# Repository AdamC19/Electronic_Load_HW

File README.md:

# Electronic_Load_HW
Hardware source files for my multi-channel electronic load. Read more about this device [here](http://www.acordingley.us/electronic-load/).
## Electronic_Load_Controller/
Files for the controller, of which there should be 1 per electronic load.
## Electronic_Load_Module/
Files for the modules/channels. I designed it to have 8 of these per electronic load.

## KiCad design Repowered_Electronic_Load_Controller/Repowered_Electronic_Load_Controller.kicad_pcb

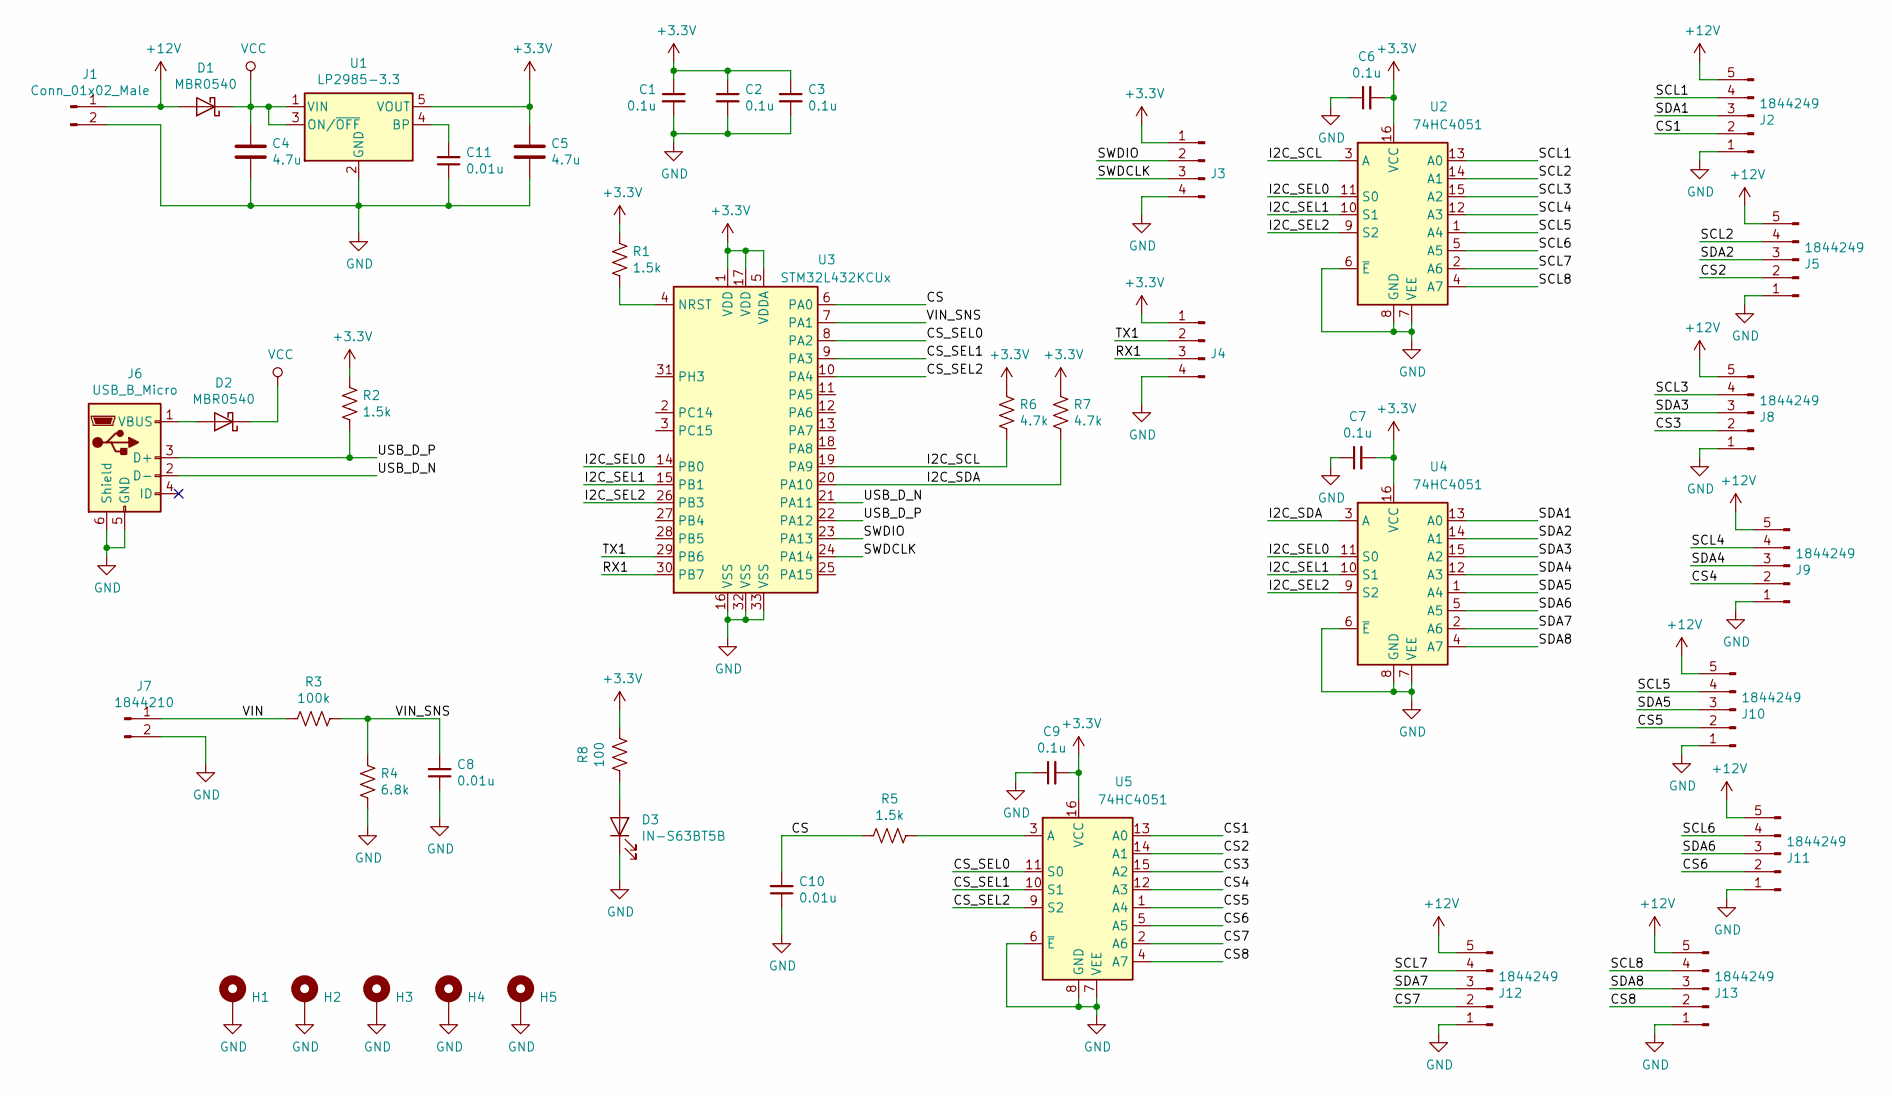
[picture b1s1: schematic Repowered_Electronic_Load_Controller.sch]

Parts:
C1, C2, C3, C6, C7, C9: 0.1u; C_0603_1608Metric
C4, C5: 4.7u; C_0805_2012Metric
C8, C10, C11: 0.01u; C_0603_1608Metric
D1, D2: MBR0540; D_SOD-123
D3: IN-S63BT5B; LED_0603_1608Metric
H1, H2, H3, H4, H5: MountingHole_Pad; MountingHole_2.5mm_Pad
J1: Conn_01x02_Male; PhoenixContact_MC_1,5_2-G-3.5_1x02_P3.50mm_Horizontal
J2, J5, J8, J9, J10, J11, J12, J13: 1844249; PhoenixContact_MC_1,5_5-G-3.5_1x05_P3.50mm_Horizontal
J3, J4: Conn_01x04_Male; PinHeader_1x04_P2.54mm_Vertical
J6: USB_B_Micro; USB_Micro-B_Molex-105017-0001
J7: 1844210; PhoenixContact_MC_1,5_2-G-3.5_1x02_P3.50mm_Horizontal
R1, R2, R5: 1.5k; R_0805_2012Metric
R3: 100k; R_0805_2012Metric
R4: 6.8k; R_0805_2012Metric
R6, R7: 4.7k; R_0805_2012Metric
R8: 100; R_0805_2012Metric
U1: LP2985-3.3; SOT-23-5
U2, U4, U5: 74HC4051; SOIC-16_3.9x9.9mm_P1.27mm
U3: STM32L432KCUx; QFN-32-1EP_5x5mm_P0.5mm_EP3.45x3.45mm

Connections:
+3V3: C1.1, C2.1, C3.1, C5.1, C6.2, C7.2, C9.2, J3.1, J4.1, R1.1, R2.1, R6.1, R7.1, R8.2, U1.5 (VOUT), U2.16 (VCC), U3.1 (VDD), U3.5 (VDDA), U3.17 (VDD), U4.16 (VCC), U5.16 (VCC)
+12V: D1.2 (A), J1.1, J2.5, J5.5, J8.5, J9.5, J10.5, J11.5, J12.5, J13.5
/CS: C10.2, R5.1, U3.6 (PA0)
/CS1: J2.2, U5.13 (A0)
/CS2: J5.2, U5.14 (A1)
/CS3: J8.2, U5.15 (A2)
/CS4: J9.2, U5.12 (A3)
/CS5: J10.2, U5.1 (A4)
/CS6: J11.2, U5.5 (A5)
/CS7: J12.2, U5.2 (A6)
/CS8: J13.2, U5.4 (A7)
/CS_SEL0: U3.8 (PA2), U5.11 (S0)
/CS_SEL1: U3.9 (PA3), U5.10 (S1)
/CS_SEL2: U3.10 (PA4), U5.9 (S2)
/I2C_SCL: R6.2, U2.3 (A), U3.19 (PA9)
/I2C_SDA: R7.2, U3.20 (PA10), U4.3 (A)
/I2C_SEL0: U2.11 (S0), U3.14 (PB0), U4.11 (S0)
/I2C_SEL1: U2.10 (S1), U3.15 (PB1), U4.10 (S1)
/I2C_SEL2: U2.9 (S2), U3.26 (PB3), U4.9 (S2)
/RX1: J4.3, U3.30 (PB7)
/SCL1: J2.4, U2.13 (A0)
/SCL2: J5.4, U2.14 (A1)
/SCL3: J8.4, U2.15 (A2)
/SCL4: J9.4, U2.12 (A3)
/SCL5: J10.4, U2.1 (A4)
/SCL6: J11.4, U2.5 (A5)
/SCL7: J12.4, U2.2 (A6)
/SCL8: J13.4, U2.4 (A7)
/SDA1: J2.3, U4.13 (A0)
/SDA2: J5.3, U4.14 (A1)
/SDA3: J8.3, U4.15 (A2)
/SDA4: J9.3, U4.12 (A3)
/SDA5: J10.3, U4.1 (A4)
/SDA6: J11.3, U4.5 (A5)
/SDA7: J12.3, U4.2 (A6)
/SDA8: J13.3, U4.4 (A7)
/SWDCLK: J3.3, U3.24 (PA14)
/SWDIO: J3.2, U3.23 (PA13)
/TX1: J4.2, U3.29 (PB6)
/USB_D_N: J6.2 (D-), U3.21 (PA11)
/USB_D_P: J6.3 (D+), R2.2, U3.22 (PA12)
/VIN: J7.1, R3.1
/VIN_SNS: C8.2, R3.2, R4.2, U3.7 (PA1)
GND: C1.2, C2.2, C3.2, C4.2, C5.2, C6.1, C7.1, C8.1, C9.1, C10.1, C11.1, D3.1 (K), H1.1, H2.1, H3.1, H4.1, H5.1, J1.2, J2.1, J3.4, J4.4, J5.1, J6.5 (GND), J6.6 (Shield), J7.2, J8.1, J9.1, J10.1, J11.1, J12.1, J13.1, R4.1, U1.2 (GND), U2.6 (~E), U2.7 (VEE), U2.8 (GND), U3.16 (VSS), U3.32 (VSS), U3.33 (VSS), U4.6 (~E), U4.7 (VEE), U4.8 (GND), U5.6 (~E), U5.7 (VEE), U5.8 (GND)
unnamed: C11.2, U1.4 (BP)
unnamed: D2.2 (A), J6.1 (VBUS)
unnamed: D3.2 (A), R8.1
unnamed: R1.2, U3.4 (NRST)
unnamed: R5.2, U5.3 (A)
VCC: C4.1, D1.1 (K), D2.1 (K), U1.1 (VIN), U1.3 (ON/~OFF~)

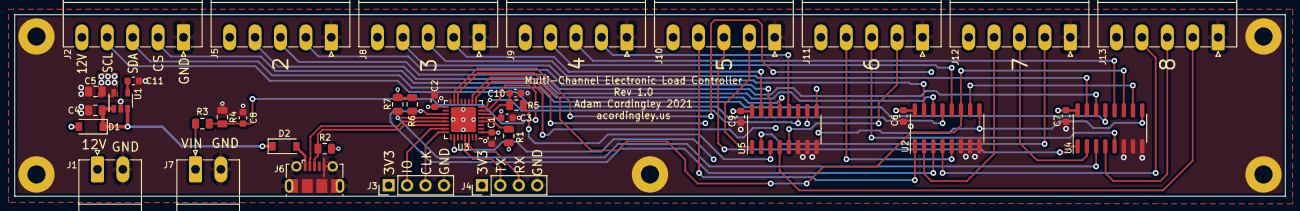
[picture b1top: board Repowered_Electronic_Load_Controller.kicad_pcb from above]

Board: 4 copper layers, 175.0 x 25.0 mm, 43 parts (0 on the bottom side), 49 nets.

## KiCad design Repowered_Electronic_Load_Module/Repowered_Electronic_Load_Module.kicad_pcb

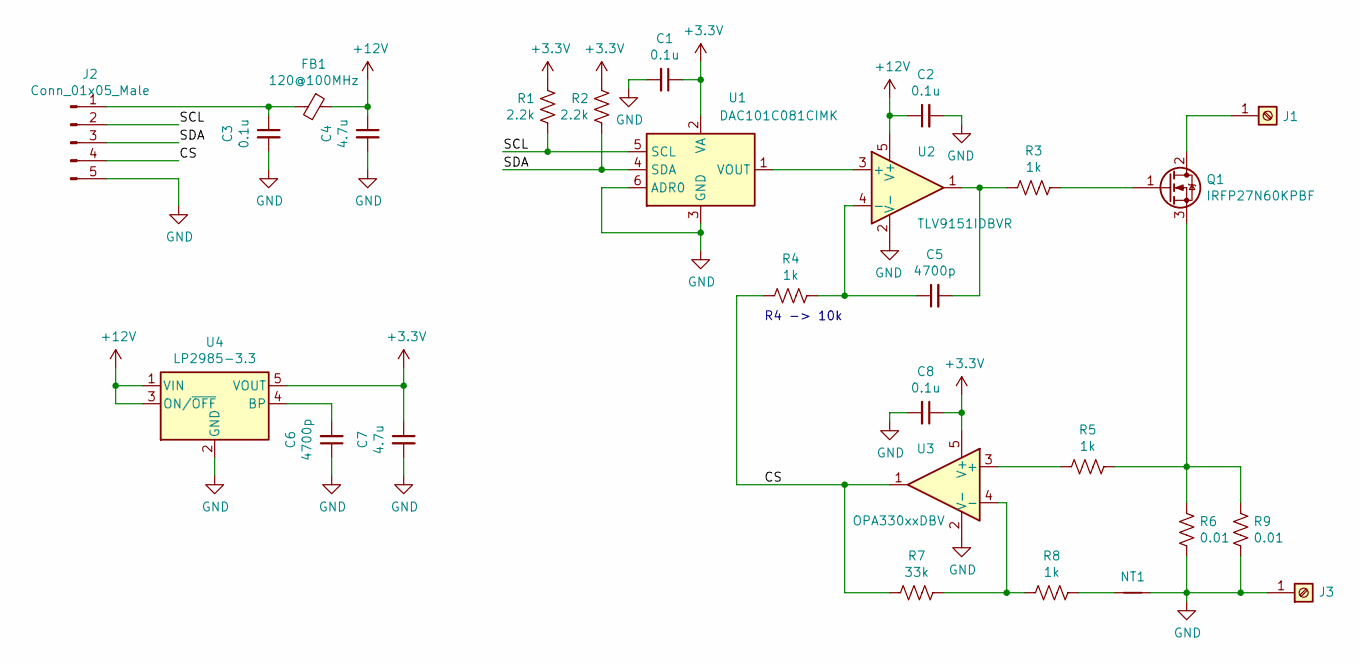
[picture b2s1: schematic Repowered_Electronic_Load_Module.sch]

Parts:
C1, C2, C3, C8: 0.1u; C_0603_1608Metric
C4, C7: 4.7u; C_0805_2012Metric
C5, C6: 4700p; C_0603_1608Metric
FB1: 120@100MHz; L_0805_2012Metric
J1, J3: Screw_Terminal_01x01; MountingHole_4.3mm_M4_Pad_Via
J2: Conn_01x05_Male; PhoenixContact_MC_1,5_5-G-3.5_1x05_P3.50mm_Horizontal
NT1: Net-Tie_2; NetTie-2_SMD_Pad0.5mm
Q1: IRFP27N60KPBF; TO-247-3_Vertical
R1, R2: 2.2k; R_0805_2012Metric
R3, R4, R5, R8: 1k; R_0805_2012Metric
R6, R9: 0.01; R_2512_6332Metric
R7: 33k; R_0805_2012Metric
U1: DAC101C081CIMK; SOT-23-6
U2: TLV9151IDBVR; SOT-23-5
U3: OPA330xxDBV; SOT-23-5
U4: LP2985-3.3; SOT-23-5

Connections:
+3V3: C1.1, C7.1, C8.1, R1.1, R2.1, U1.2 (VA), U3.5 (V+), U4.5 (VOUT)
+12V: C2.1, C4.1, FB1.1, U2.5 (V+), U4.1 (VIN), U4.3 (ON/~OFF~)
/CS: J2.4, R4.2, R7.2, U3.1
/SCL: J2.2, R1.2, U1.5 (SCL)
/SDA: J2.3, R2.2, U1.4 (SDA)
GND: C1.2, C2.2, C3.2, C4.2, C6.1, C7.2, C8.2, J2.5, J3.1, NT1.2, R6.2, R9.2, U1.3 (GND), U1.6 (ADR0), U2.2 (V-), U3.2 (V-), U4.2 (GND)
unnamed: C3.1, FB1.2, J2.1
unnamed: C5.1, R4.1, U2.4 (-)
unnamed: C5.2, R3.2, U2.1
unnamed: C6.2, U4.4 (BP)
unnamed: J1.1, Q1.2 (D)
unnamed: NT1.1, R8.1
unnamed: Q1.1 (G), R3.1
unnamed: Q1.3 (S), R5.1, R6.1, R9.1
unnamed: R5.2, U3.3 (+)
unnamed: R7.1, R8.2, U3.4 (-)
unnamed: U1.1 (VOUT), U2.3 (+)

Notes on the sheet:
R4 -> 10k

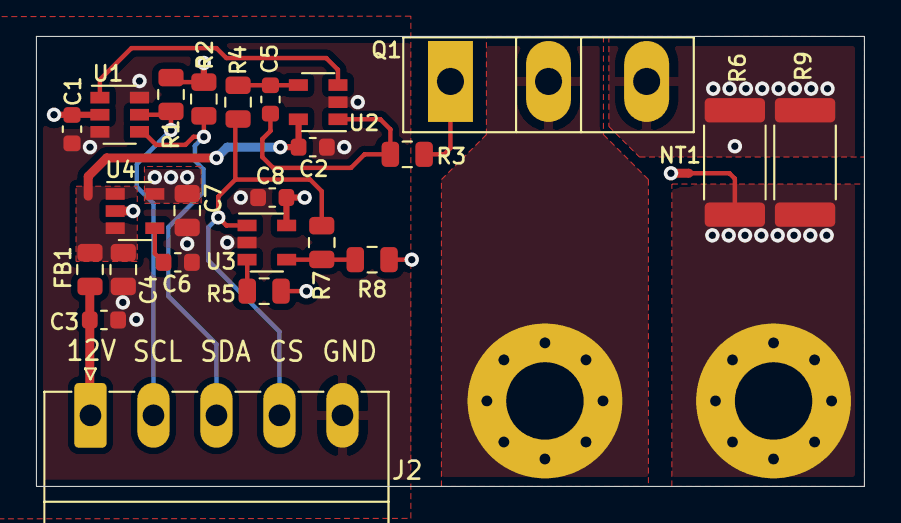
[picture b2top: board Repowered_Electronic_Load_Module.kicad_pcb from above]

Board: 4 copper layers, 46.0 x 25.0 mm, 27 parts (0 on the bottom side), 17 nets.

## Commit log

2021-10-04 Add link to website article.
2021-10-04 Fix link
